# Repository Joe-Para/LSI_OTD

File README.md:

# LSI_OTD

A project for building the hardware and software for measuring time delay on fiber cables in distributed measurmeent systems.

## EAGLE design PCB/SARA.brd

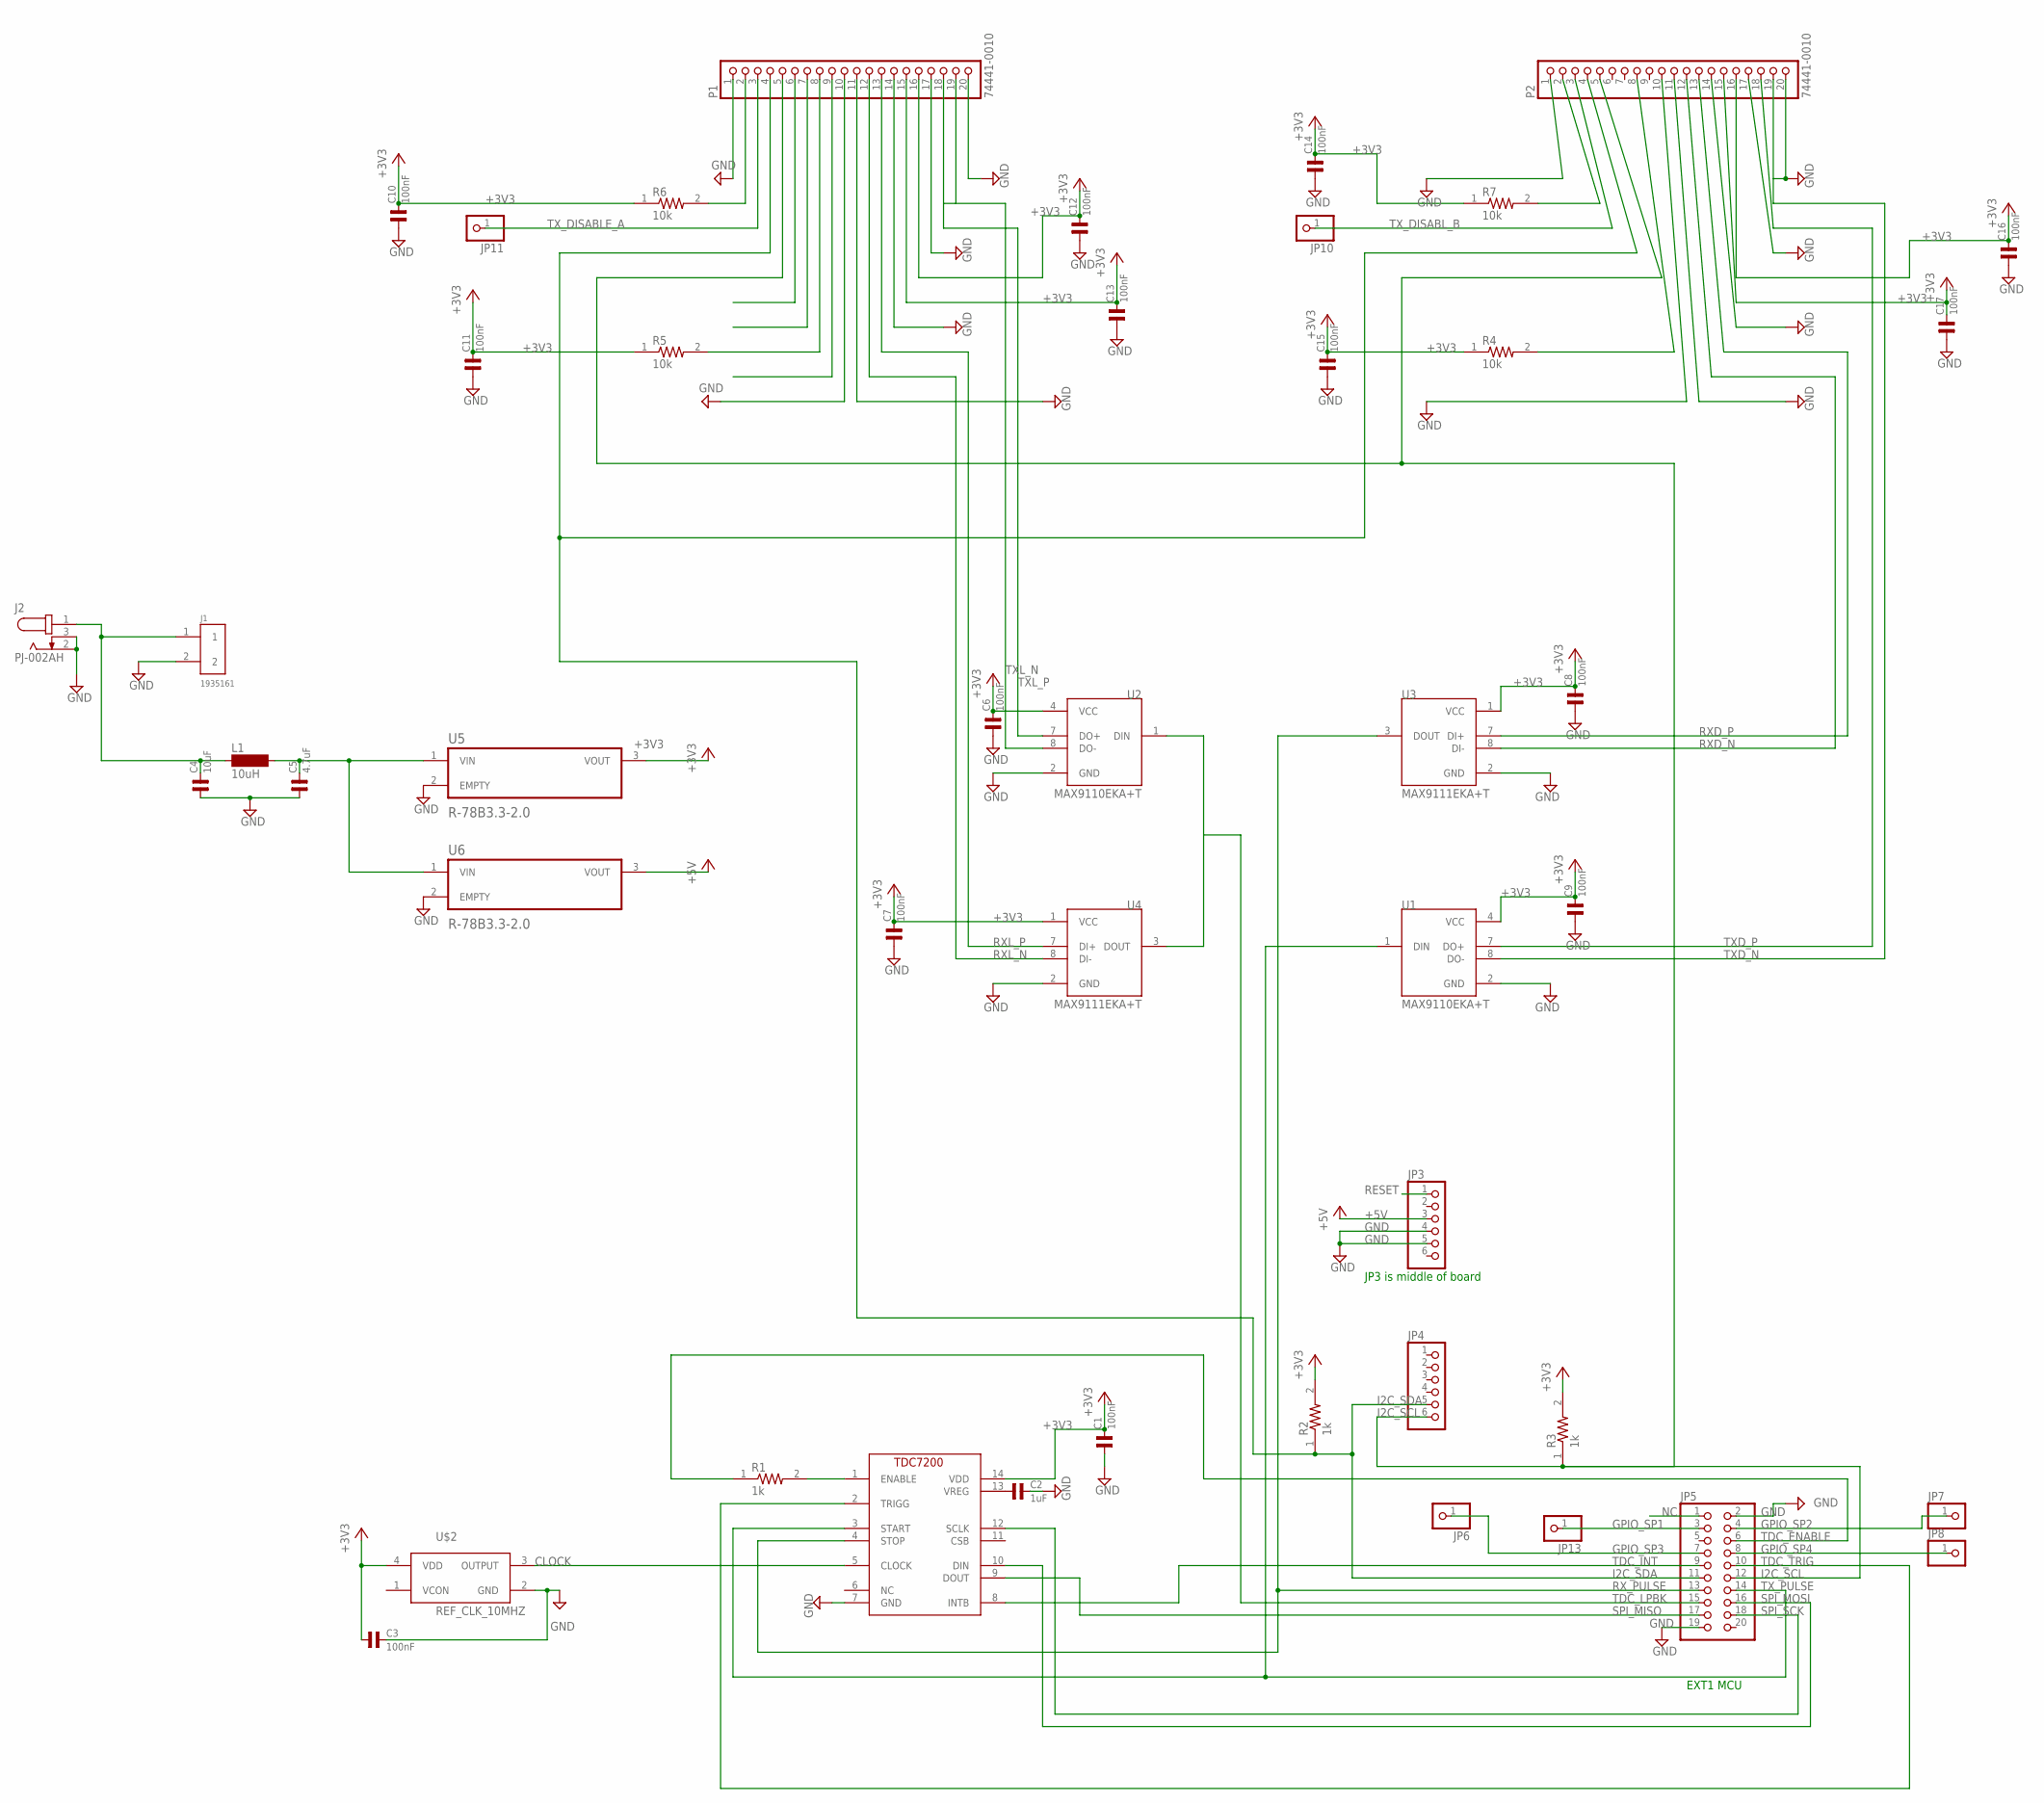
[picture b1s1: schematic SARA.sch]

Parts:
C1, C3, C6, C7, C8, C9, C10, C11, C12, C13, C14, C15, C16, C17: 100nF; 0603
C2: 1uF; 0603
C4: 10uF; 0603
C5: 4.7uF; 0603
J1: 1935161; PHOENIX_1935161
J2: PJ-002AH; CUI_PJ-002AH
JP3, JP4: PINHD-1X6; 1X06
JP5: PINHD-2X10; 2X10
JP6, JP7, JP8, JP10, JP11, JP13: PINHD-1X1; 1X01
L1: 10uH; MS50
P1, P2: 74441-0010; MOLEX_74441-0010
R1, R2, R3: 1k; RESC1608X55
R4, R5, R6, R7: 10k; RESC1608X55
U1, U2: MAX9110EKA+T; SOT65P280X145-8N
U3, U4: MAX9111EKA+T; SOT65P280X145-8N
U5, U6: R-78B3.3-2.0; CONV_R-78B15-2.0
U$1: TDC72007201PW; SOP65P640X120-14N
U$2: REF_CLK_10MHZ; TWETMCJANF-10.000000

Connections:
+3V3: C1.2, C3.1, C6.2, C7.2, C8.2, C9.2, C10.2, C11.2, C12.2, C13.2, C14.2, C15.2, C16.2, C17.2, P1.15, P1.16, P2.15, P2.16, R2.2, R3.2, R4.1, R5.1, R6.1, R7.1, U1.4 (VCC), U2.4 (VCC), U3.1 (VCC), U4.1 (VCC), U5.3 (VOUT), U$1.14 (VDD), U$2.4 (VDD)
+5V: JP3.3, U6.3 (VOUT)
CLOCK: U$1.5 (CLOCK), U$2.3 (OUTPUT)
GND: C1.1, C2.2, C3.2, C4.1, C5.1, C6.1, C7.1, C8.1, C9.1, C10.1, C11.1, C12.1, C13.1, C14.1, C15.1, C16.1, C17.1, J1.2, J2.2, J2.3, JP3.4, JP3.5, JP5.2, JP5.19, P1.1, P1.10, P1.11, P1.14, P1.17, P1.20, P2.1, P2.11, P2.14, P2.17, P2.20, U1.2 (GND), U2.2 (GND), U3.2 (GND), U4.2 (GND), U5.2 (EMPTY), U6.2 (EMPTY), U$1.7 (GND), U$2.2 (GND)
GPIO_SP1: JP5.3, JP13.1
GPIO_SP2: JP5.4, JP7.1
GPIO_SP3: JP5.7, JP6.1
GPIO_SP4: JP5.8, JP8.1
I2C_SCL: JP4.6, JP5.12, P1.5, P2.5, R3.1
I2C_SDA: JP4.5, JP5.11, P1.4, P2.4, R2.1
unnamed: P2.8, R4.2
unnamed: R1.2, U$1.1 (ENABLE)
unnamed: C2.1, U$1.13 (VREG)
unnamed: C5.2, L1.2, U5.1 (VIN), U6.1 (VIN)
unnamed: U2.1 (DIN), U4.3 (DOUT)
unnamed: P1.8, R5.2
unnamed: P1.2, R6.2
unnamed: P2.2, R7.2
unnamed: C4.2, J1.1, J2.1, L1.1
NC: JP5.1
RESET: JP3.1
RXD_N: P2.12, U3.8 (DI-)
RXD_P: P2.13, U3.7 (DI+)
RXL_N: P1.12, U4.8 (DI-)
RXL_P: P1.13, U4.7 (DI+)
RX_PULSE: JP5.13, U3.3 (DOUT), U$1.4 (STOP)
SPI_MISO: JP5.17, U$1.9 (DOUT)
SPI_MOSI: JP5.16, U$1.10 (DIN)
SPI_SCK: JP5.18, U$1.12 (SCLK)
TDC_ENABLE: JP5.6, R1.1
TDC_INT: JP5.9, U$1.8 (INTB)
TDC_LPBK: JP5.15
TDC_TRIG: JP5.10, U$1.2 (TRIGG)
TXD_N: P2.19, U1.8 (DO-)
TXD_P: P2.18, U1.7 (DO+)
TXL_N: P1.19, U2.8 (DO-)
TXL_P: P1.18, U2.7 (DO+)
TX_DISABLE_A: JP11.1, P1.3
TX_DISABL_B: JP10.1, P2.3
TX_PULSE: JP5.14, U1.1 (DIN), U$1.3 (START)

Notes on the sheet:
JP3 is middle of board
EXT1 MCU

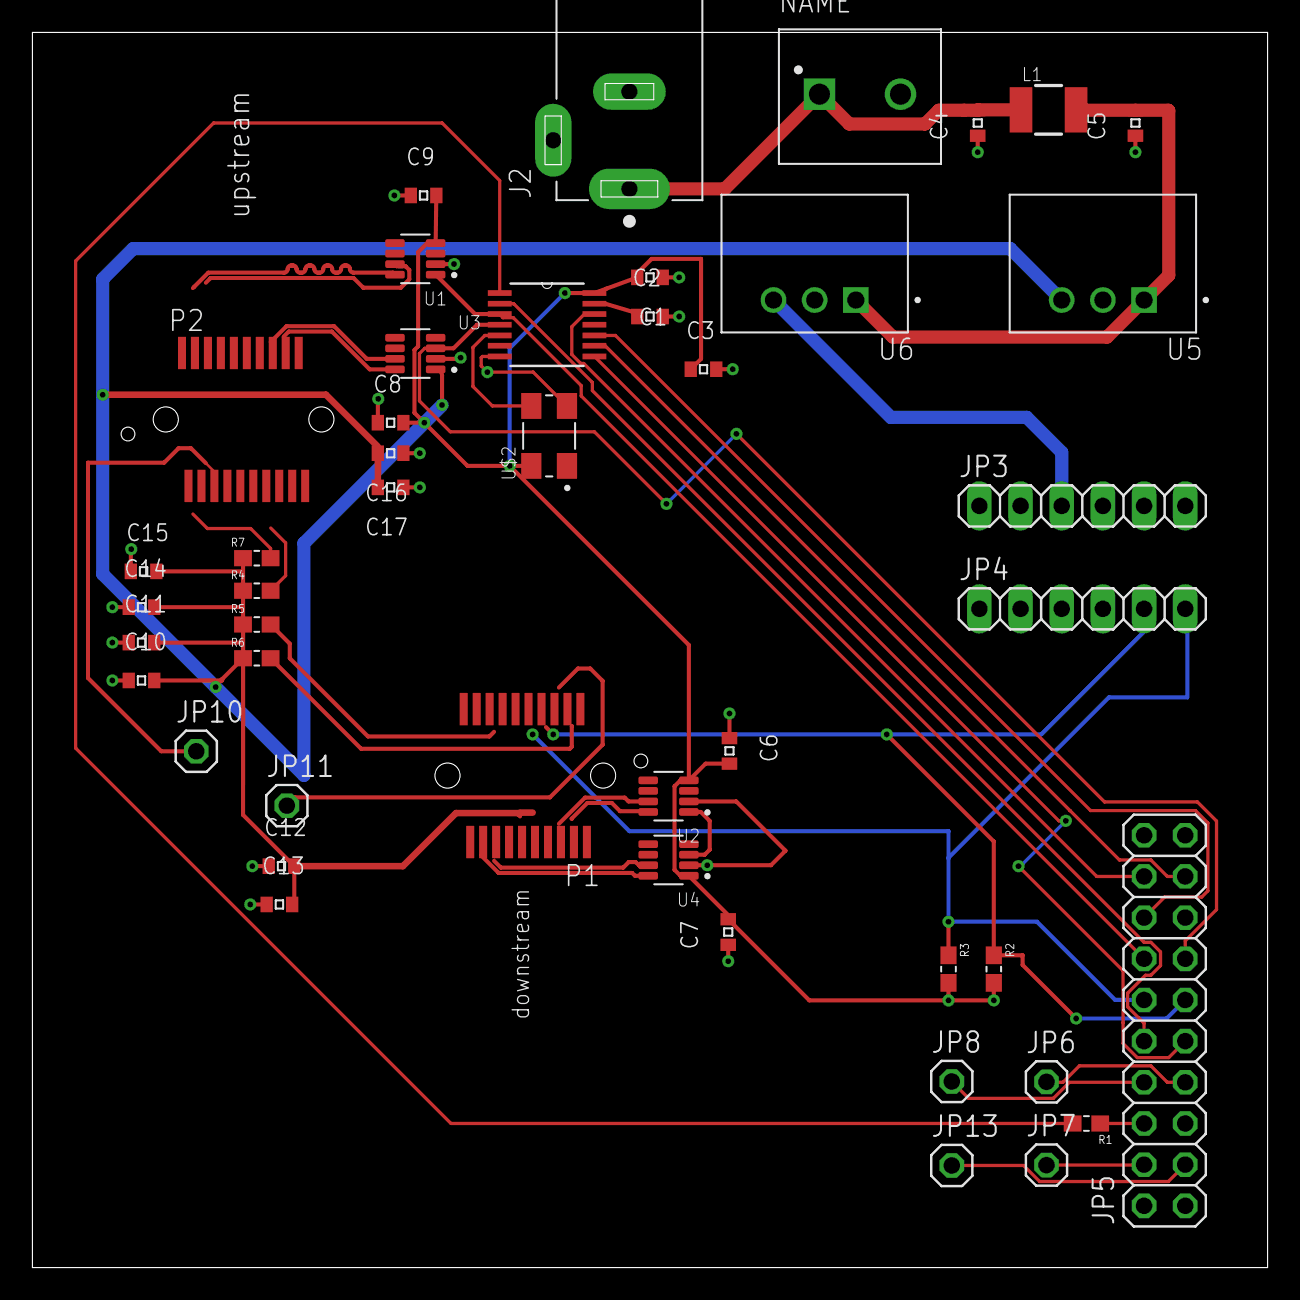
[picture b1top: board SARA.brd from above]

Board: 2 copper layers, 76.2 x 76.2 mm, 46 parts (0 on the bottom side), 37 nets.

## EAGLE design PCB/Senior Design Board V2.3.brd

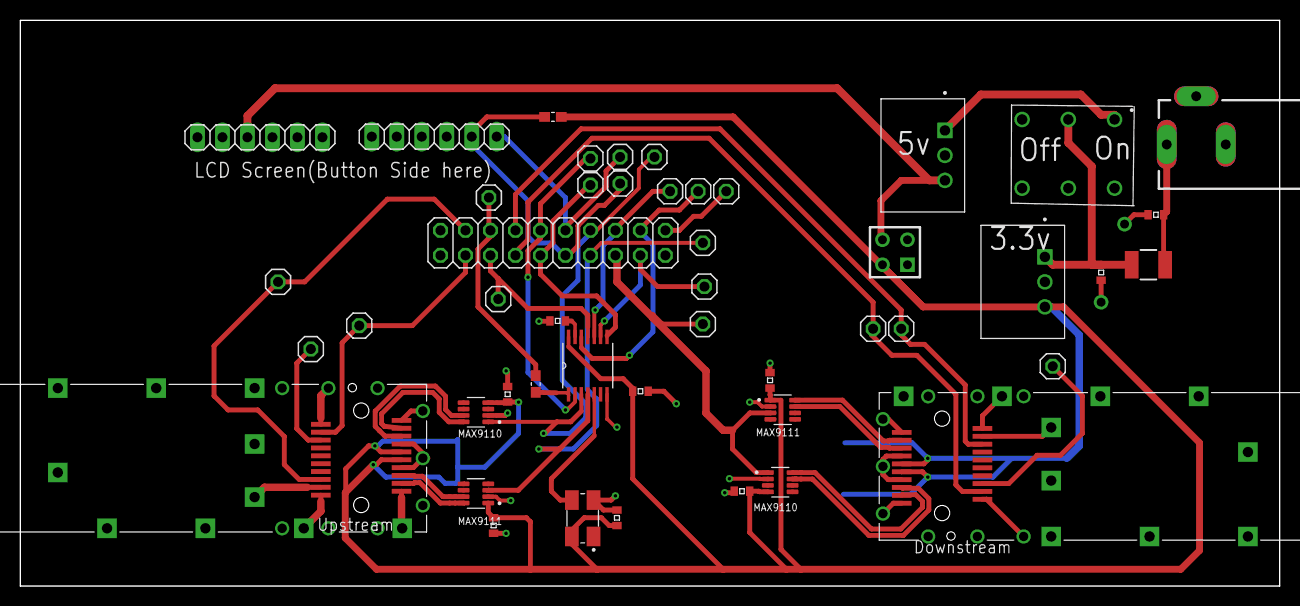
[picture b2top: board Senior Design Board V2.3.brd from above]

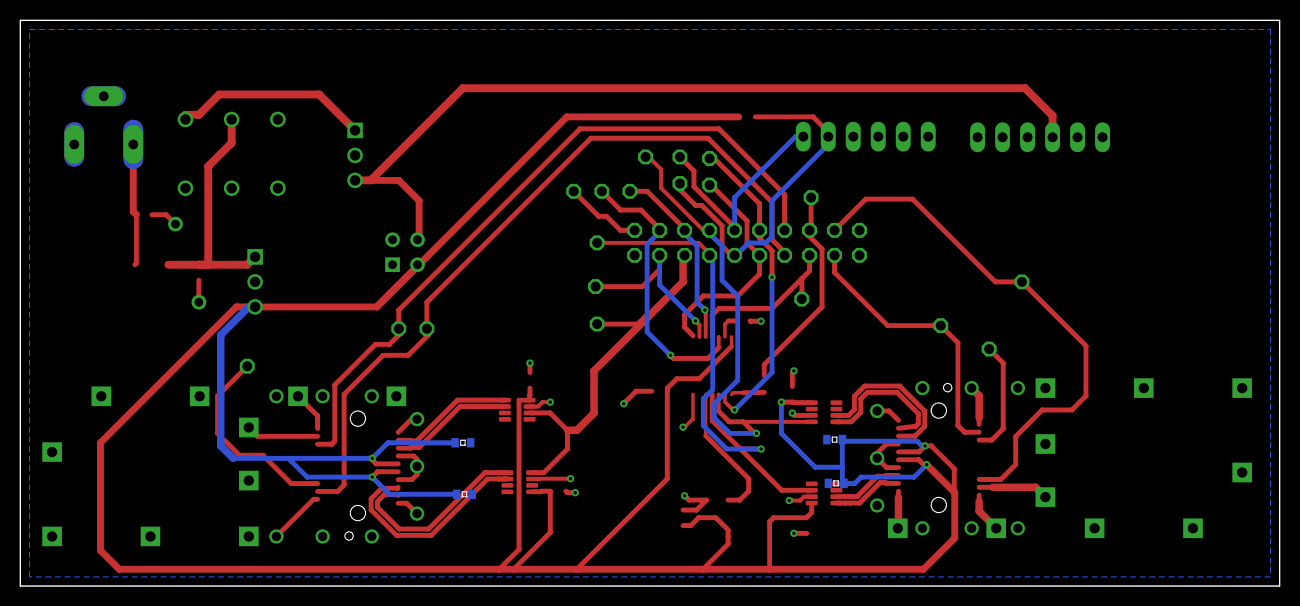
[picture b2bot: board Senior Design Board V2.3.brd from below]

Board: 2 copper layers, 128.0 x 57.5 mm, 53 parts (4 on the bottom side), 36 nets.

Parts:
C1: .1uf; 0603
C2: 1uF; 0603_C2
C3, C11, C18: 100nF; 0603
C4: 10uF; 0603_C2
C5: 4.7uF; 0603
C6: 100nF; 0603_C6
C14: 100nF; 0603_C2
C19, C20, C21, C22: 100nF; 0603_C19
GPIO_SPARE1, GPIO_SPARE2, GPIO_SPARE3, GPIO_SPARE4: 1X01
J1: 4840-2211
J3: HDR-2X2
JP3, JP4: 1X06
JP5: 2X10
JP10, JP11: 1X01
L1: 10uH; MS50
PAD63, PAD80: PAD
R1: 1k; RESC1608X55
R2: 1k; RESC1608X55_R2
SW1: DEV_SW1; P137
TDC: TDC72007201PW; SOP65P640X120-14N
TESTPIN5, TESTPIN6: 1X01
TP9, TP10, TP11, TP12, TP13, TP14, TP15, TP16, TP18, TP20: 1X01
TP_17: 1X01
U1, U2: MAX9110EKA+T; SOT65P280X145-8N
U3, U4: MAX9111EKA+T; SOT65P280X145-8N
U5, U6: R-78B3.3-2.0; CONV_R-78B15-2.0
U7: DEV_U7; P159
U8: DEV_U8; P17
U$2: REF_CLK_10MHZ; TWETMCJANF-10.000000

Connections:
3.3_V: C1.2, C3.2, C6.1, C11.2, C14.2, C18.1, C19.2, C20.2, C21.1, C22.1, J3.2, R2.2, TDC.14, U1.4, U2.4, U3.1, U4.1, U5.3, U7.15, U7.16, U8.15, U8.16, U$2.4
12V: C5.2, L1.2, SW1.3_3, U5.1
+5V: J3.4, JP3.3, U6.3
CLOCK: TDC.5, U$2.3
I2C_SCL: JP4.6, JP5.12, TP12.1
I2C_SDA: JP4.5, JP5.11, R2.1, TP11.1
unnamed: C2.1, TDC.13
unnamed: C4.2, J1.1, L1.1
NET_0: SW1.2_1, U6.1
NET_35: JP5.20, TP20.1
POWER_GROUND: C1.1, C2.2, C3.1, C4.1, C5.1, C6.2, C11.1, C14.1, C18.2, C19.1, C20.1, C21.2, C22.2, J1.2, J1.3, J3.1, JP3.5, JP5.2, JP5.19, PAD63.1, PAD80.1, SW1.3_1, SW1.3_2, TDC.7, U1.2, U2.2, U3.2, U4.2, U5.2, U6.2, U7.1, U7.9, U7.10, U7.11, U7.14, U7.17, U7.20, U7.S1, U7.S2, U7.S3, U7.S5, U7.S6, U7.S7, U7.S8, U7.S9, U7.S10, U7.S11, U7.S12, U7.S13, U7.S14, U7.S15, U7.S16, U7.S17, U7.S18, U7.S19, U7.S20, U8.1, U8.9, U8.10, U8.11, U8.14, U8.17, U8.20, U8.S1, U8.S2, U8.S3, U8.S5, U8.S6, U8.S7, U8.S8, U8.S9, U8.S10, U8.S11, U8.S12, U8.S13, U8.S14, U8.S15, U8.S16, U8.S17, U8.S18, U8.S19, U8.S20, U$2.2
RD_DOWN_N: U4.8, U8.12
RD_DOWN_P: U4.7, U8.13
RD_UP_N: U3.8, U7.12
RD_UP_P: U3.7, U7.13
RX_LOSS_DOWN: GPIO_SPARE4.1, JP5.8, U8.8
RX_LOSS_UP: GPIO_SPARE2.1, JP5.4, U7.8
RX_PULSE: JP5.13, TDC.4, TP13.1, U3.3
SPI_MISO: JP5.17, TDC.9, TP_17.1
SPI_MOSI: JP5.16, TDC.10, TP16.1
SPI_SCK: JP5.18, TDC.12, TP18.1
TDC_CSB: JP5.5, TDC.11, TESTPIN5.1
TDC_ENABLE: R1.2, TDC.1
TDC_ENABLE_1: JP5.6, R1.1, TESTPIN6.1
TDC_INT: JP5.9, TDC.8, TP9.1
TDC_LPBK: JP5.15, TP15.1, U2.1, U4.3
TDC_TRIG: JP5.10, TDC.2, TP10.1
TD_DOWN_N: U2.8, U8.19
TD_DOWN_P: U2.7, U8.18
TD_UP_N: U1.8, U7.19
TD_UP_P: U1.7, U7.18
TX_DISABLE_DOWN: JP11.1, U8.3
TX_DISABLE_UP: JP10.1, U7.3
TX_FAULT_DOWN: GPIO_SPARE3.1, JP5.7, U8.2
TX_FAULT_UP: GPIO_SPARE1.1, JP5.3, U7.2
TX_PULSE: JP5.14, TDC.3, TP14.1, U1.1

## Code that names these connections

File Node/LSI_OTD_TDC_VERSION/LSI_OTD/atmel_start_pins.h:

/*
 * Code generated from Atmel Start.
 *
 * This file will be overwritten when reconfiguring your Atmel Start project.
 * Please copy examples or other code you want to keep to a separate file
 * to avoid losing it when reconfiguring.
 */
#ifndef ATMEL_START_PINS_H_INCLUDED
#define ATMEL_START_PINS_H_INCLUDED

#include <hal_gpio.h>

// SAME70 has 4 pin functions

#define GPIO_PIN_FUNCTION_A 0
#define GPIO_PIN_FUNCTION_B 1
#define GPIO_PIN_FUNCTION_C 2
#define GPIO_PIN_FUNCTION_D 3

#define TX_FAULT_DOWN GPIO(GPIO_PORTA, 0)

#define I2C0_SDA GPIO(GPIO_PORTA, 3)
#define I2C0_SCL GPIO(GPIO_PORTA, 4)
#define RX_LOSS_UP GPIO(GPIO_PORTA, 19)
#define PA21 GPIO(GPIO_PORTA, 21)
#define RX_PULSE GPIO(GPIO_PORTB, 0)
#define TX_PULSE GPIO(GPIO_PORTB, 1)
#define TDC_ENABLE GPIO(GPIO_PORTB, 2)
#define SPI0_SS GPIO(GPIO_PORTB, 3)
#define PB4 GPIO(GPIO_PORTB, 4)
#define PHY_RESET_PIN GPIO(GPIO_PORTC, 10)
#define TDC_TRIG GPIO(GPIO_PORTC, 17)
#define RX_LOSS_DOWN GPIO(GPIO_PORTC, 30)
#define TX_FAULT_UP GPIO(GPIO_PORTC, 31)
#define PD0 GPIO(GPIO_PORTD, 0)
#define PD1 GPIO(GPIO_PORTD, 1)
#define PD2 GPIO(GPIO_PORTD, 2)
#define PD3 GPIO(GPIO_PORTD, 3)
#define PD4 GPIO(GPIO_PORTD, 4)
#define PD5 GPIO(GPIO_PORTD, 5)
#define PD6 GPIO(GPIO_PORTD, 6)
#define PD7 GPIO(GPIO_PORTD, 7)
#define PD8 GPIO(GPIO_PORTD, 8)
#define PD9 GPIO(GPIO_PORTD, 9)
#define SPI0_MISO GPIO(GPIO_PORTD, 20)
#define SPI0_MOSI GPIO(GPIO_PORTD, 21)
#define SPI0_SCK GPIO(GPIO_PORTD, 22)
#define TDC_LPBK GPIO(GPIO_PORTD, 25)
#define TDC_INT GPIO(GPIO_PORTD, 28)
#define LED0 GPIO(GPIO_PORTC, 8)

#define TX_DISABLE_UP GPIO(GPIO_PORTD, 30)
#define TX_DISABLE_DOWN GPIO(GPIO_PORTC, 13)

#endif // ATMEL_START_PINS_H_INCLUDED

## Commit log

2019-03-13 initial folder structure
2019-04-03 Backlink to CADLAB.io has been added.
2019-04-03 added eagle files
2019-04-03 Create Folder Structure
2019-04-03 Node + Workstation Folders w/ Workstation Program & Interrupt Program
2019-04-03 added tdc proto
2019-04-03 gitIgnore fot Atmel Studios and Visual Studios
2019-04-04 renamed EXT1 pins and named differential traces
2019-04-04 90% done routing, renamed stuff and added differental traces.
2019-04-08 Working Node TCP Client
2019-04-08 Working Workstation TCP Server - Works with node Working TCP Client
2019-04-08 changed host to '' from 'localhost'; fixed message recv
2019-04-09 Finished Proto 1 PCB from cameron
2019-04-10 Fixed node prototype - working tcp client. Ready for demo.
2019-04-10 Modified Workstation Protype for demo
2019-04-10 Rename .gitignore.txt to .gitignore
    should fix sourcetree's trying to commmit my atsuo files
2019-04-10 removed .atsuo files
2019-04-10 gitignore fix
2019-04-11 Renaming node "Working TCP Client" to "Working TCP Client - ASF3"
2019-04-11 Working TCP Client working on ASF4
2019-04-12 added atmel start with all components
2019-04-12 unpacked ATMEL START
2019-04-12 integrated "lwif example asf4" into final project
2019-04-12 enabled LWIF DEBUG, beware your console output :D
2019-04-12 Removing Ethernet.c...junk file I created that we didn't need
2019-04-12 Finalized Workstation Program
2019-04-12 Cleaned up "main.c". Put all communications setup into its own .h and .c files
2019-04-12 Added comments in runCommand function in main.c
2019-04-12 Modified Workstation "Working TCP Server" to be able to send any command to node and receive its reply
2019-04-12 Renamed pcb to TCPpcb & modified runCommand function to ensure each command sends a reply back to workstation
2019-04-12 Fixed communicationCount, added MC_PORT and SC_PORT for config
2019-04-12 Fixed typos in setup errors
2019-04-12 Added workstation config file and added functionality to print errors to .error file
2019-04-12 Added .error files to gitignore for workstations error file
2019-04-13 SPI setup added
2019-04-13 added tdc driver
2019-04-13 fixed include and typing bugs for spi and tdc
2019-04-13 added TDC_DEBUG macro, can now use TDC_DEBUG(message) for handy printf to serial output. can be mass disabled by TDC_DEBUG_ON set to 0
2019-04-14 comments
2019-04-15 added code for start_tof
2019-04-15 Added ISRs and flags variable
2019-04-16 Added main.h for flag & state definitions
2019-04-16 Changed flags in ISR, setup states, added functionality to Send Ping, Listen, Stop Listening
2019-04-16 Fixed typos in tdc7200
2019-04-16 Set timeout in workstation tcp server
2019-04-16 Started flag handling
2019-04-16 Added Stop Listening command to workstation and made minor fixes
2019-04-16 Fixed Flag handling
2019-04-17 added i2c stuff
2019-04-17 added multicycle averaging to TDC file
2019-04-17 Fixed merge errors
2019-04-17 Fixed bugs in workstation program: did not send ping, error to string, setting nodes to listen
2019-04-17 Disable all LWIP debugging + fixed Ping sent message error
2019-04-18 Fixed TCPpcb naming error
2019-04-18 Added Second connection flag
2019-04-18 Workstation - added SC_TIMEOUT
2019-04-19 fixed i2c not showing up in project
2019-04-19 ported adafruit dislay library to our solution ~~untested~~
2019-04-23 LCD WORKING....FINALLY
2019-04-25 Node modifications for second connect
2019-04-25 Changed GPIO spares to TX_Fault and RX_Loss
2019-04-25 Fixed typo in pull mode for TX_FAULT_DOWN
2019-04-26 Communication Setup fixed
2019-04-26 Set pull down resistors on interrupt pins
2019-04-26 Added state command & isrEnable flags
2019-04-26 New Workstation not using input and outputs to determine order
2019-05-01 manual merged in tdc7200.c and .h
2019-05-01 refixed
2019-05-03 Thursday Working TDC w/ up to date other stuff
2019-05-04 Friday working stuff with tx_disable(low output) & rx_loss(pull-up resistor)
2019-05-05 Current Debug state.....RX_Pulse is sent to output for testing TDC
2019-05-08 Workting TDC stuff...DO NOT TOUCH!!!!!
2019-05-08 Separte File for Node-TDC software - Working
2019-05-09 New Node Update?
2019-05-10 Current Node + Workstation...Ready for Final Demo
2019-05-12 Master Clean Up & Comments - Workstation
2019-05-13 Master cleanup & comments - remove node prototype code
2019-05-13 Master Cleanup & Comment - Node Files
2019-05-14 Added Tim's PCB v2 files
2019-05-14 Workstation Clean up + comment - node's main.c
2019-05-14 Update README.md
    deleted to do list.
